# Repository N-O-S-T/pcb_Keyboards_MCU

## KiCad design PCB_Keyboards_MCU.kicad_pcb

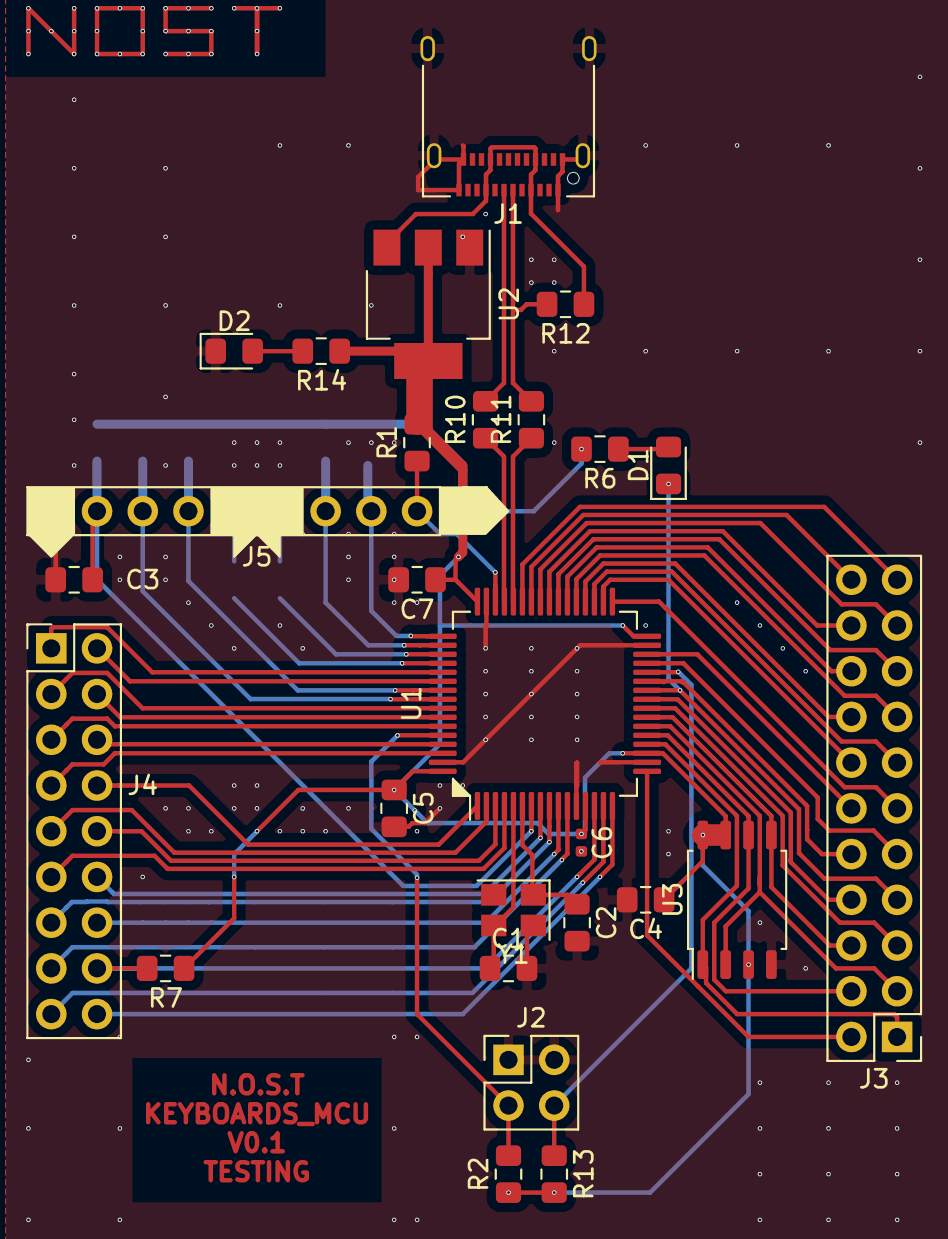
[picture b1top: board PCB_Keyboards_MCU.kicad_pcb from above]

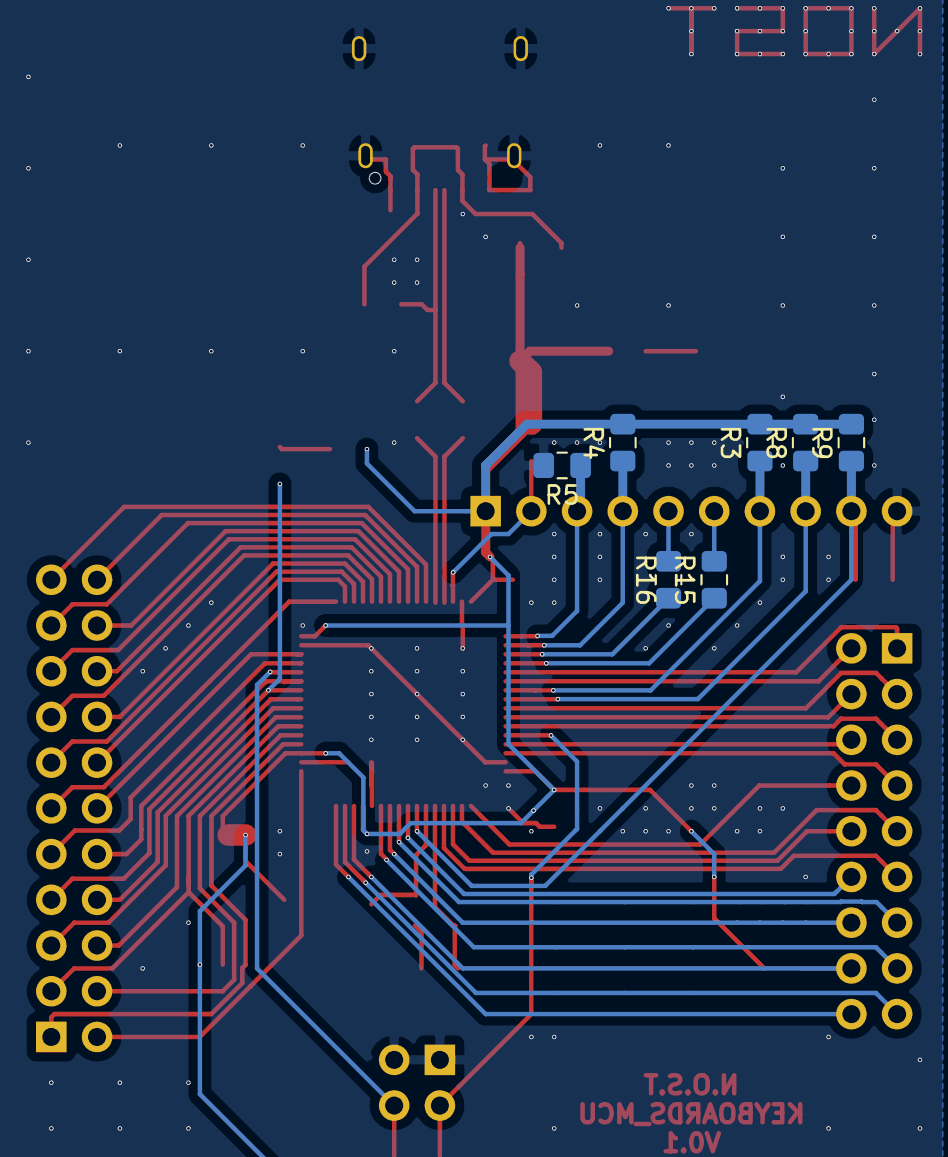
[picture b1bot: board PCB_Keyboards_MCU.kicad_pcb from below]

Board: 2 copper layers, 34 parts (7 on the bottom side), 63 nets.

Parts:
C1, C2, C3, C4, C5, C7: C_Small; C_0805_2012Metric_Pad1.15x1.40mm_HandSolder
C6: C_Small; C_0402_1005Metric
D1, D2: LED; LED_0805_2012Metric_Pad1.15x1.40mm_HandSolder
J1: USB_C_Receptacle_USB2.0; USB_C_Receptacle_Amphenol_12401610E4-2A
J2: Conn_02x02_Odd_Even; PinHeader_2x02_P2.54mm_Vertical
J3: Conn_02x11_Odd_Even; PinHeader_2x11_P2.54mm_Vertical
J4: Conn_02x09_Odd_Even; PinHeader_2x09_P2.54mm_Vertical
J5: Conn_01x10; PinHeader_1x10_P2.54mm_Vertical
R1, R2, R3, R4, R5, R6, R7, R8, R9, R10, R11, R12, R13, R14, R15, R16: R_Small; R_0805_2012Metric_Pad1.15x1.40mm_HandSolder
U1: STM32F103RBT6; LQFP-64_10x10mm_P0.5mm
U2: AMS1117-3.3; SOT-223-3_TabPin2
U3: W25Q32JVSS; SOIC-8_5.23x5.23mm_P1.27mm
Y1: Crystal_GND24_Small; Crystal_SMD_3225-4Pin_3.2x2.5mm

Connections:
/3.3V: C4.1, C5.1, C6.1, C7.1, J5.1, R1.2, R2.1, R3.2, R4.2, R6.2, R7.1, R8.2, R9.2, R13.2, R14.1, U1.13, U1.19, U1.32, U1.48, U1.64, U2.2, U3.3, U3.7, U3.8
/5V: J1.A4, J1.A9, J1.B4, J1.B9, R12.1, U2.3
/BOOT0: J2.3, R2.2, U1.60
/BOOT1: J2.4, R13.1, U1.28
/D+: J1.A6, J1.B6, R11.2, R12.2
/D-: J1.A7, J1.B7, R10.2
/NRST: C3.1, J5.9, R9.1, U1.7
/PA0: J4.16, R7.2, U1.14
/PA1: J4.17, U1.15
/PA2: J4.18, U1.16
/PA3: J3.2, U1.17
/PA4: J3.1, U1.20, U3.1
/PA5: J3.4, U1.21, U3.6
/PA6: J3.3, U1.22, U3.2
/PA7: J3.6, U1.23, U3.5
/PA8: J3.19, U1.41
/PA9: J3.22, U1.42
/PA10: J3.21, U1.43
/PA13: J5.2, R1.1, U1.46
/PA14: J5.3, R5.1, U1.49
/PA15: J5.4, R4.1, U1.50
/PB0: D1.1, J3.7, U1.26
/PB1: J3.10, U1.27
/PB3: J5.7, R3.1, U1.55
/PB4: J5.8, R8.1, U1.56
/PB5: J4.3, U1.57
/PB6: J4.4, U1.58
/PB7: J4.5, U1.59
/PB8: J4.6, U1.61
/PB9: J4.7, U1.62
/PB10: J3.9, U1.29
/PB11: J3.12, U1.30
/PB12: J3.11, U1.33
/PB13: J3.14, U1.34
/PB14: J3.13, U1.35
/PB15: J3.16, U1.36
/PC0: J4.12, U1.8
/PC1: J4.13, U1.9
/PC2: J4.14, U1.10
/PC3: J4.15, U1.11
/PC4: J3.5, U1.24
/PC5: J3.8, U1.25
/PC6: J3.15, U1.37
/PC7: J3.18, U1.38
/PC8: J3.17, U1.39
/PC9: J3.20, U1.40
/PC10: R16.1, U1.51
/PC11: R15.1, U1.52
/PC12: J4.1, U1.53
/PC13: J4.9, U1.2
/PC14: J4.10, U1.3
/PC15: J4.11, U1.4
/PD0: C1.1, U1.5, Y1.3
/PD1: C2.1, U1.6, Y1.1
/PD2: J4.2, U1.54
/S+: R11.1, U1.44
/S-: R10.1, U1.45
/VBAT: J4.8, U1.1
GND: C1.2, C2.2, C3.2, C4.2, C5.2, C6.2, C7.2, D2.1, J1.A1, J1.A12, J1.B1, J1.B12, J1.S1, J2.1, J2.2, J5.10, R5.2, U1.12, U1.18, U1.31, U1.47, U1.63, U2.1, U3.4, Y1.2, Y1.4
unnamed: D1.2, R6.1
unnamed: D2.2, R14.2
unnamed: J5.5, R16.2
unnamed: J5.6, R15.2

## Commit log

2019-11-18 工程文件
